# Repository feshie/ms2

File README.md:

# ms2
second version of the feshie node with the z1 replaced with a plug-in arm processor (TI CC2538)

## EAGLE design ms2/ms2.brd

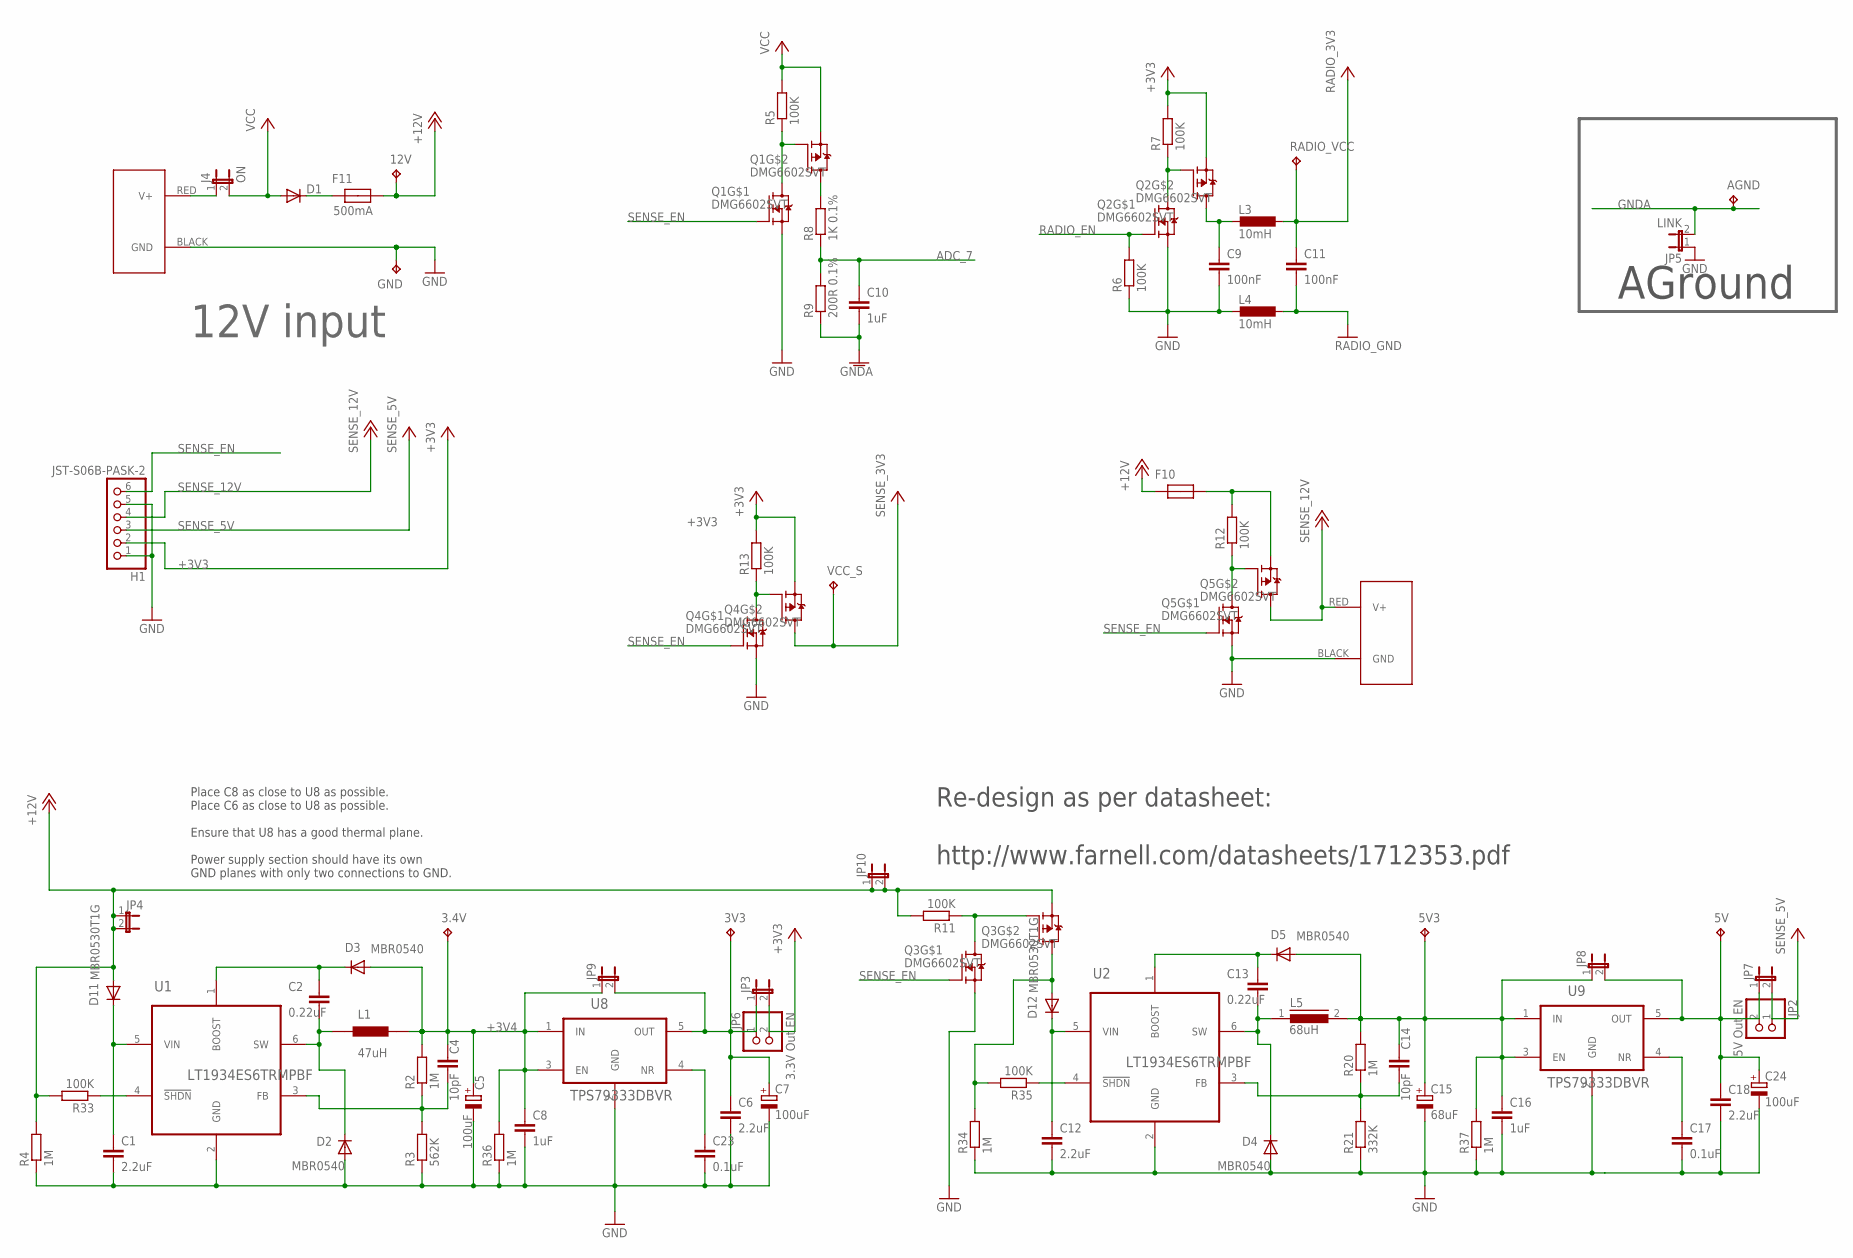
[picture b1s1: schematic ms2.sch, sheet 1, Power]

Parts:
3.4V, 3V3, 12V: TPB2,54; B2,54
5V, 5V3: 5V B; B2,54
12V_OUT: POWERPOLE_POWER45A; POWERPOLE_PAIR_45A
AGND: TPB2,54; B2,54
C1, C6, C12, C18: 2.2uF; C0805
C2, C13: 0.22uF; C0805
C4, C14: 10pF; C0805
C5, C7, C24: 100uF; PANASONIC_E
C8, C10, C16: 1uF; C0805
C9, C11: 100nF; C0805
C15: 68uF; PANASONIC_E
C17, C23: 0.1uF; C0805
D1: DIODE-SMB; SMB
D2, D3, D4, D5: MBR0540; SOD123
D11, D12: MBR0530T1G; SOD123
F10, F11: MCF0805; 0805
GND: 5V B; B2,54
H1: JST-S06B-PASK-2; JST-PA-6-SE
J1: POWERPOLE_POWER45A; POWERPOLE_PAIR_45A
J4: ON; 2-MOLEX
JP2: 5V Out EN; 1X02
JP3, JP4, JP7, JP8, JP9, JP10: JUMPER-2SMD-NO; SJ_2S-NO
JP5: LINK; JP1
JP6: 3.3V Out EN; 1X02
L1: 47uH; 1048
L3, L4: 10mH; L3230M
L5: 68uH; DR127
Q1, Q2, Q3, Q4, Q5: DMG6602SVT; TSOT26
R2, R4, R20, R34, R36, R37: 1M; R0805
R3: 562K; R0805
R5, R6, R7, R11, R12, R13, R33, R35: 100K; R0805
R8: 1K 0.1%; R0805
R9: 200R 0.1%; R0805
R21: 332K; R0805
RADIO_VCC: TPB2,54; B2,54
U1, U2: LT1934ES6TRMPBF; SOT95P280X100-6N
U8, U9: TPS79333DBVR; SOT95P280X145-5N
VCC_S: TPB2,54; B2,54

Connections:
5V3: 5V3.TP, C14.1, C15.+, C16.1, D5.A, JP8.1, L5.2, R20.2, R37.2, U9.1 (IN), U9.3 (EN)
+3V3: H1.2, JP3.2, JP6.2, Q2.P$2 (S), Q4.P$2 (S), R7.2, R13.2; also elsewhere on the board
+3V4: 3.4V.TP, C4.1, C5.+, C8.1, D3.A, JP9.1, L1.2, R2.2, R36.2, U8.1 (IN), U8.3 (EN)
+12V: 12V.TP, D11.A, F10.1, F11.2, JP4.1, JP4.2, JP10.1, JP10.2, Q3.P$2 (S), R4.2, R11.2, R33.2
ADC_7: C10.1, R8.1, R9.2; also elsewhere on the board
GND: 12V_OUT.BLACK (GND), C1.2, C5.-, C6.2, C7.-, C8.2, C9.2, C12.2, C15.-, C16.2, C17.2, C18.2, C23.2, C24.-, D2.A, D4.A, GND.TP, H1.1, H1.5, J1.BLACK (GND), JP5.1, L4.2, Q1.P$5 (S), Q2.P$5 (S), Q3.P$5 (S), Q4.P$5 (S), Q5.P$5 (S), R3.1, R4.1, R6.1, R21.1, R34.1, R36.1, R37.1, U1.2 (GND), U2.2 (GND), U8.2 (GND), U9.2 (GND); also elsewhere on the board
GNDA: AGND.TP, C10.2, JP5.2, R9.1; also elsewhere on the board
unnamed: J1.RED (V+), J4.1
unnamed: C13.1, D5.C, U2.1 (BOOST)
unnamed: D1.C, F11.1
unnamed: C23.1, U8.4 (NR)
unnamed: Q2.P$3 (G), Q2.P$6 (D), R7.1
unnamed: Q1.P$3 (G), Q1.P$6 (D), R5.1
unnamed: 5V.TP, C18.1, C24.+, JP2.2, JP7.1, JP8.2, U9.5 (OUT)
unnamed: C9.1, L3.2, Q2.P$4 (D)
unnamed: Q3.P$3 (G), Q3.P$6 (D), R11.1
unnamed: Q4.P$3 (G), Q4.P$6 (D), R13.1
unnamed: C12.1, D12.C, U2.5 (VIN)
unnamed: C13.2, D4.C, L5.1, U2.6 (SW)
unnamed: C4.2, R2.1, R3.2, U1.3 (FB)
unnamed: 3V3.TP, C6.1, C7.+, JP3.1, JP6.1, JP9.2, U8.5 (OUT)
unnamed: C14.2, R20.1, R21.2, U2.3 (FB)
unnamed: Q5.P$3 (G), Q5.P$6 (D), R12.1
unnamed: F10.2, Q5.P$2 (S), R12.2
unnamed: C1.1, D11.C, U1.5 (VIN)
unnamed: R33.1, U1.4 (!SHDN)
unnamed: R35.1, U2.4 (!SHDN)
unnamed: D12.A, Q3.P$4 (D), R34.2, R35.2
unnamed: C17.1, U9.4 (NR)
unnamed: C2.2, D2.C, L1.1, U1.6 (SW)
unnamed: C2.1, D3.C, U1.1 (BOOST)
RADIO_3V3: C11.1, L3.1, RADIO_VCC.TP; also elsewhere on the board
RADIO_EN: Q2.P$1 (G), R6.2; also elsewhere on the board
RADIO_GND: C11.2, L4.1; also elsewhere on the board
SENSE_3V3: Q4.P$4 (D), VCC_S.TP; also elsewhere on the board
SENSE_5V: H1.3, JP2.1, JP7.2; also elsewhere on the board
SENSE_12V: 12V_OUT.RED (V+), H1.4, Q5.P$4 (D); also elsewhere on the board
SENSE_EN: H1.6, Q1.P$1 (G), Q3.P$1 (G), Q4.P$1 (G), Q5.P$1 (G); also elsewhere on the board
VCC: D1.A, J4.2, Q1.P$2 (S), R5.2; also elsewhere on the board
VCC_HP2_SW1: Q1.P$4 (D), R8.2

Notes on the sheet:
12V input
AGround
Re-design as per datasheet: http://www.farnell.com/datasheets/1712353.pdf
Place C8 as close to U8 as possible. Place C6 as close to U8 as possible. Ensure that U8 has a good thermal plane. Power supply section should have its own GND planes with only two connections to GND.
500mA

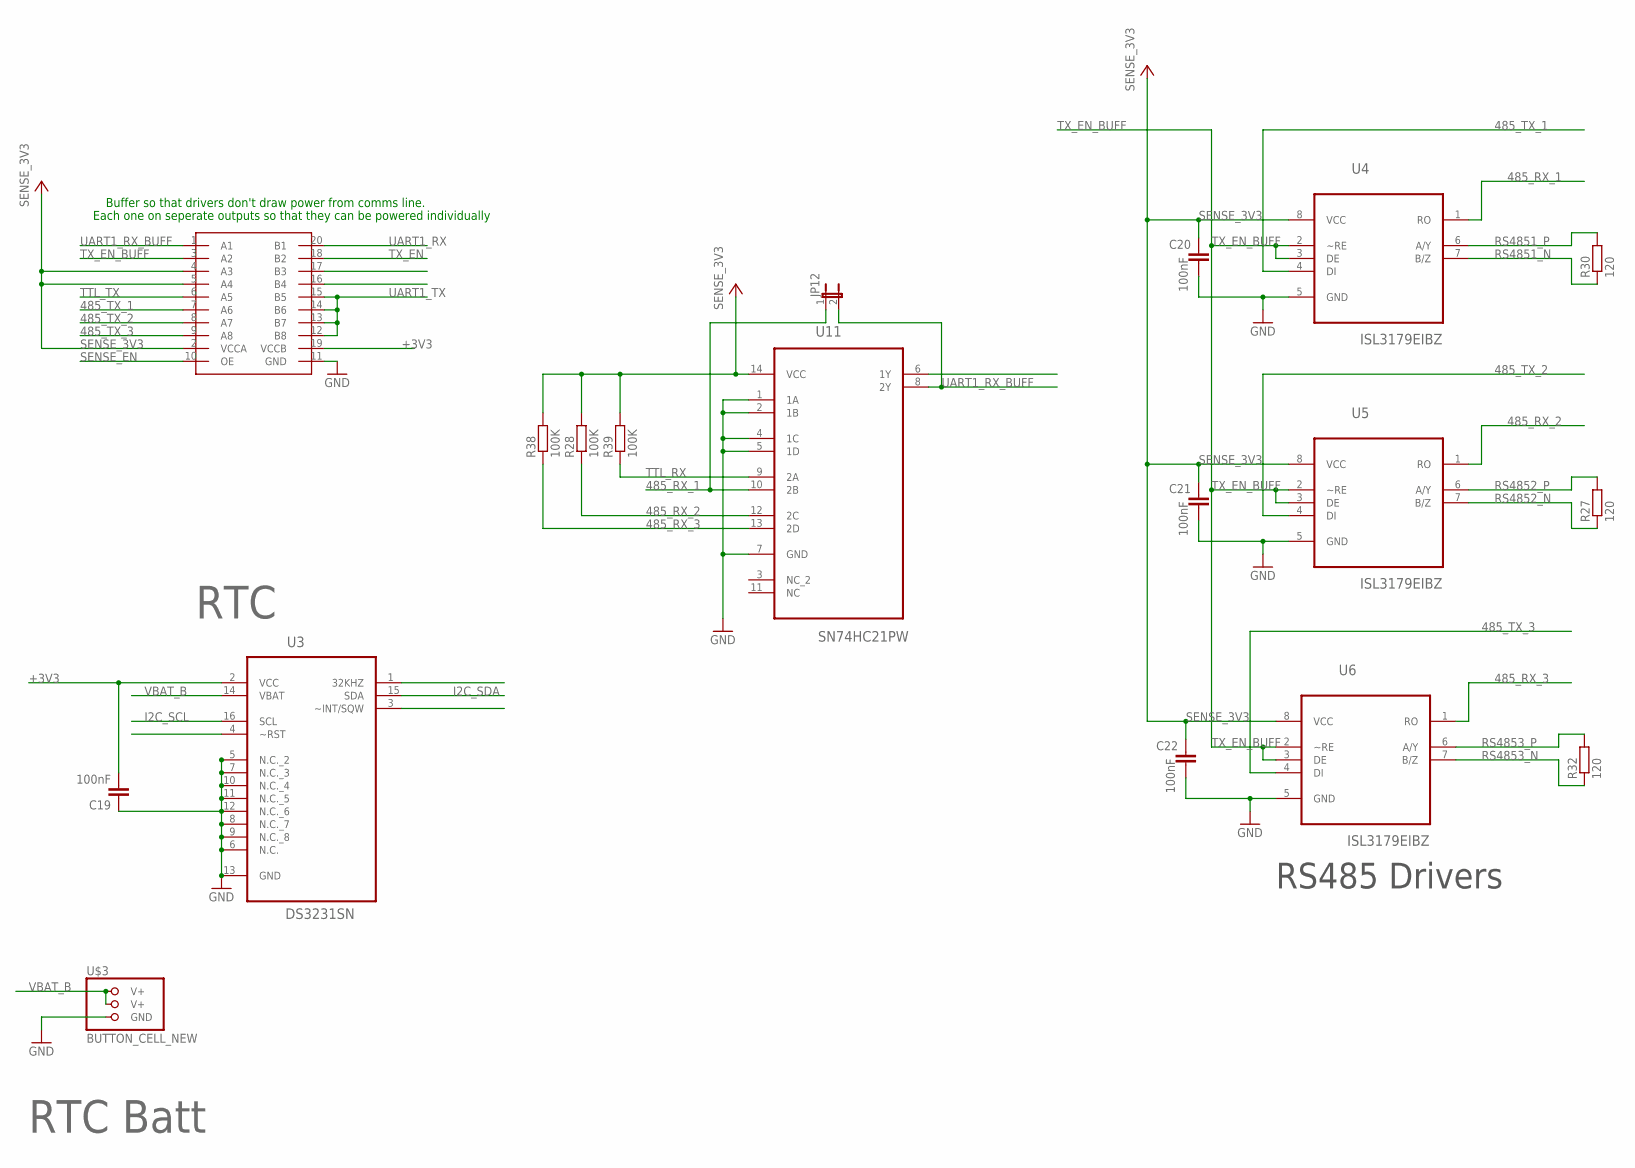
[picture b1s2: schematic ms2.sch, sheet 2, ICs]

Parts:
C19, C20, C21, C22: 100nF; C0805
JP12: JUMPER-2SMD-NO; SJ_2S-NO
R27, R30, R32: 120; R0805
R28, R38, R39: 100K; R0805
U3: DS3231SN; SOIC127P1032X265-16N
U4, U5, U6: ISL3179EIBZ; SOIC127P600X175-8N
U10: TXS0108E; TSSOP20
U11: SN74HC21PW; SOP65P640X120-14N
U$3: BUTTON_CELL_NEW; CR2016

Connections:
485_RX_1: JP12.1, U4.1 (RO), U11.10 (2B)
485_RX_2: R28.1, U5.1 (RO), U11.12 (2C)
485_RX_3: R38.1, U6.1 (RO), U11.13 (2D)
485_TX_1: U4.4 (DI), U10.7 (A6)
485_TX_2: U5.4 (DI), U10.8 (A7)
485_TX_3: U6.4 (DI), U10.9 (A8)
+3V3: C19.2, U3.2 (VCC), U10.19 (VCCB); also elsewhere on the board
GND: C19.1, C20.2, C21.2, C22.2, U3.5 (N.C._2), U3.6 (N.C.), U3.7 (N.C._3), U3.8 (N.C._7), U3.9 (N.C._8), U3.10 (N.C._4), U3.11 (N.C._5), U3.12 (N.C._6), U3.13 (GND), U4.5 (GND), U5.5 (GND), U6.5 (GND), U10.11 (GND), U11.1 (1A), U11.2 (1B), U11.4 (1C), U11.5 (1D), U11.7 (GND), U$3.GND; also elsewhere on the board
I2C_SCL: U3.16 (SCL); also elsewhere on the board
I2C_SDA: U3.15 (SDA); also elsewhere on the board
RS4851_N: R30.1, U4.7 (B/Z); also elsewhere on the board
RS4851_P: R30.2, U4.6 (A/Y); also elsewhere on the board
RS4852_N: R27.1, U5.7 (B/Z); also elsewhere on the board
RS4852_P: R27.2, U5.6 (A/Y); also elsewhere on the board
RS4853_N: R32.1, U6.7 (B/Z); also elsewhere on the board
RS4853_P: R32.2, U6.6 (A/Y); also elsewhere on the board
SENSE_3V3: C20.1, C21.1, C22.1, R28.2, R38.2, R39.2, U4.8 (VCC), U5.8 (VCC), U6.8 (VCC), U10.2 (VCCA), U10.4 (A3), U10.5 (A4), U11.14 (VCC); also elsewhere on the board
SENSE_EN: U10.10 (OE); also elsewhere on the board
TTL_RX: R39.1, U11.9 (2A); also elsewhere on the board
TTL_TX: U10.6 (A5); also elsewhere on the board
TX_EN: U10.18 (B2); also elsewhere on the board
TX_EN_BUFF: U4.2 (~RE), U4.3 (DE), U5.2 (~RE), U5.3 (DE), U6.2 (~RE), U6.3 (DE), U10.3 (A2)
UART1_RX: U10.20 (B1); also elsewhere on the board
UART1_RX_BUFF: JP12.2, U10.1 (A1), U11.8 (2Y)
UART1_TX: U10.12 (B8), U10.13 (B7), U10.14 (B6), U10.15 (B5); also elsewhere on the board
VBAT_B: U3.14 (VBAT), U$3.V+@1 (V+), U$3.V+@2 (V+)

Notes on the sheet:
RTC
RS485 Drivers
Buffer so that drivers don't draw power from comms line.
Each one on seperate outputs so that they can be powered individually
RTC Batt

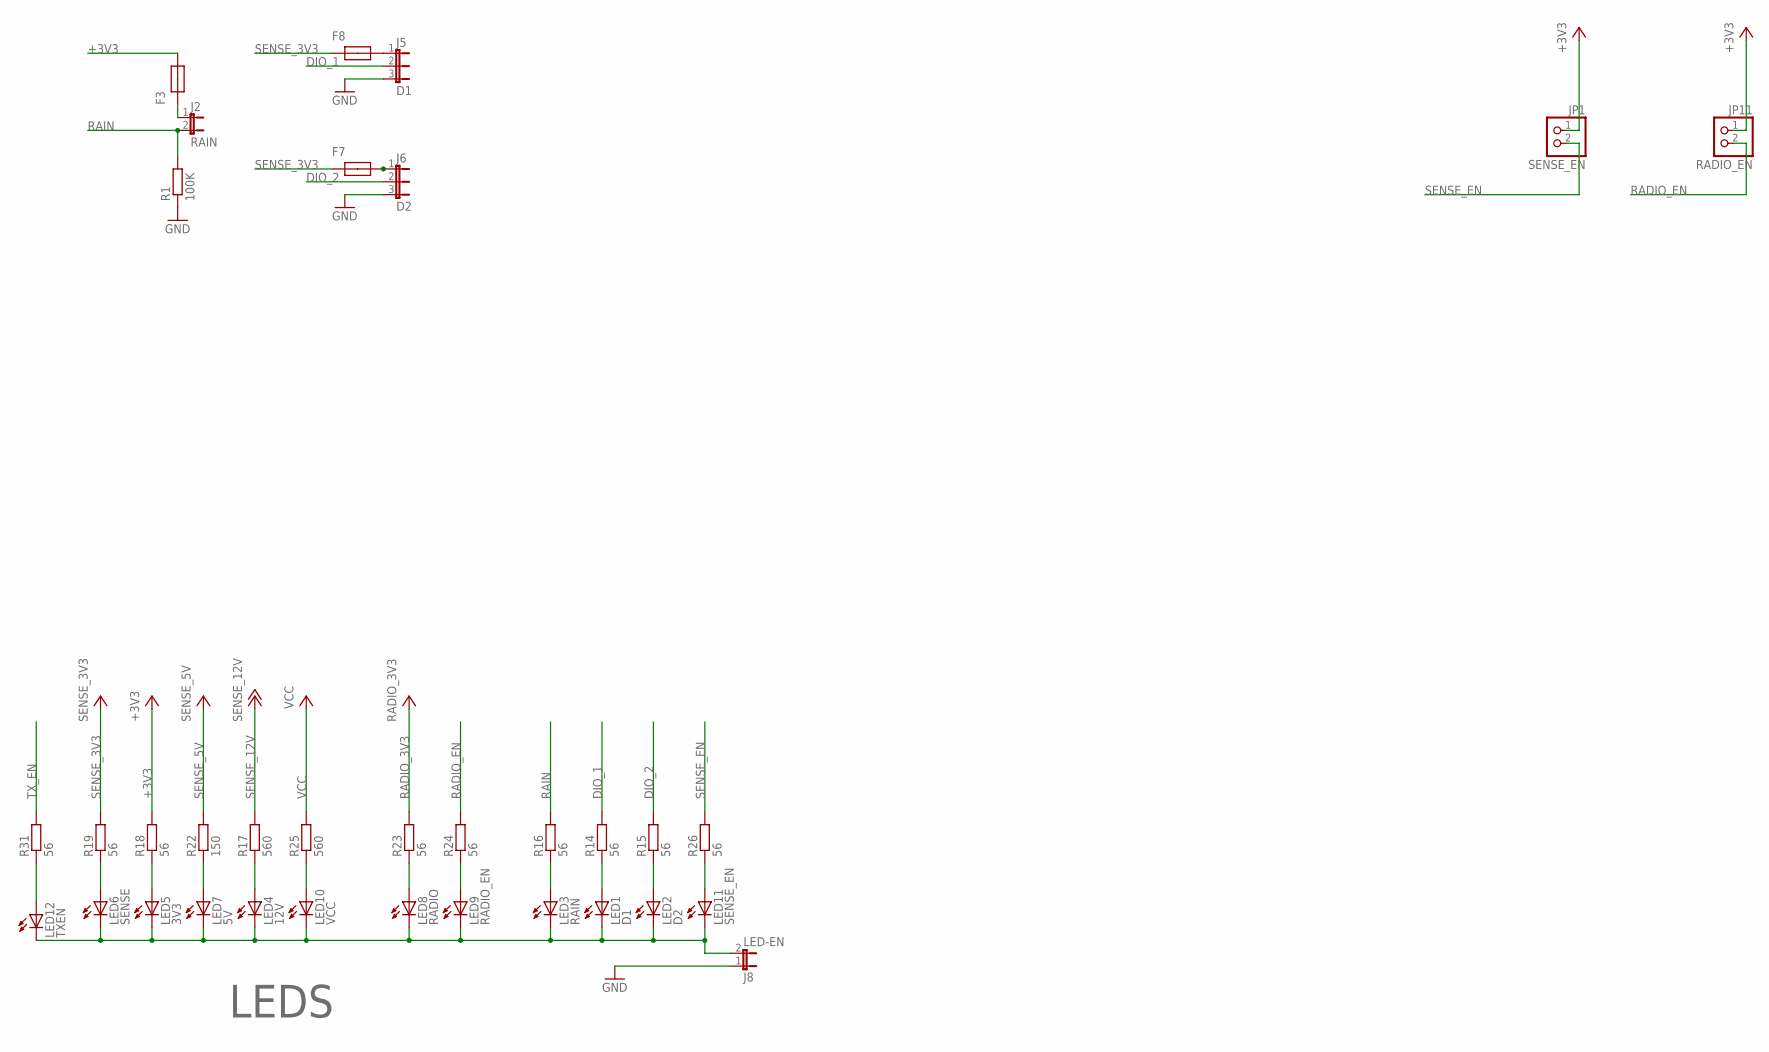
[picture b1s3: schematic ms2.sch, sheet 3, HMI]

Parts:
F3, F7, F8: MCF0805; 0805
J2: RAIN; 2-MOLEX
J5: D1; 3-MOLEX
J6: D2; 3-MOLEX
J8: LED-EN; 2-MOLEX
JP1: SENSE_EN; 1X02
JP11: RADIO_EN; 1X02
LED1: D1; CHIP-LED0805
LED2: D2; CHIP-LED0805
LED3: RAIN; CHIP-LED0805
LED4: 12V; CHIP-LED0805
LED5: 3V3; CHIP-LED0805
LED6: SENSE; CHIP-LED0805
LED7: 5V; CHIP-LED0805
LED8: RADIO; CHIP-LED0805
LED9: RADIO_EN; CHIP-LED0805
LED10: VCC; CHIP-LED0805
LED11: SENSE_EN; CHIP-LED0805
LED12: TXEN; CHIP-LED0805
R1: 100K; R0805
R14, R15, R16, R18, R19, R23, R24, R26, R31: 56; R0805
R17, R25: 560; R0805
R22: 150; R0805

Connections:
+3V3: F3.2, JP1.1, JP11.1, R18.2; also elsewhere on the board
DIO_1: J5.2, R14.2; also elsewhere on the board
DIO_2: J6.2, R15.2; also elsewhere on the board
GND: J5.3, J6.3, J8.1, R1.1; also elsewhere on the board
LGND: J8.2, LED1.C, LED2.C, LED3.C, LED4.C, LED5.C, LED6.C, LED7.C, LED8.C, LED9.C, LED10.C, LED11.C, LED12.C
unnamed: LED4.A, R17.1
unnamed: LED9.A, R24.1
unnamed: LED3.A, R16.1
unnamed: LED2.A, R15.1
unnamed: F7.2, J6.1
unnamed: F8.2, J5.1
unnamed: LED1.A, R14.1
unnamed: F3.1, J2.1
unnamed: LED12.A, R31.1
unnamed: LED11.A, R26.1
unnamed: LED10.A, R25.1
unnamed: LED8.A, R23.1
unnamed: LED7.A, R22.1
unnamed: LED6.A, R19.1
unnamed: LED5.A, R18.1
RADIO_3V3: R23.2; also elsewhere on the board
RADIO_EN: JP11.2, R24.2; also elsewhere on the board
RAIN: J2.2, R1.2, R16.2; also elsewhere on the board
SENSE_3V3: F7.1, F8.1, R19.2; also elsewhere on the board
SENSE_5V: R22.2; also elsewhere on the board
SENSE_12V: R17.2; also elsewhere on the board
SENSE_EN: JP1.2, R26.2; also elsewhere on the board
TX_EN: R31.2; also elsewhere on the board
VCC: R25.2; also elsewhere on the board

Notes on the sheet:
LEDS

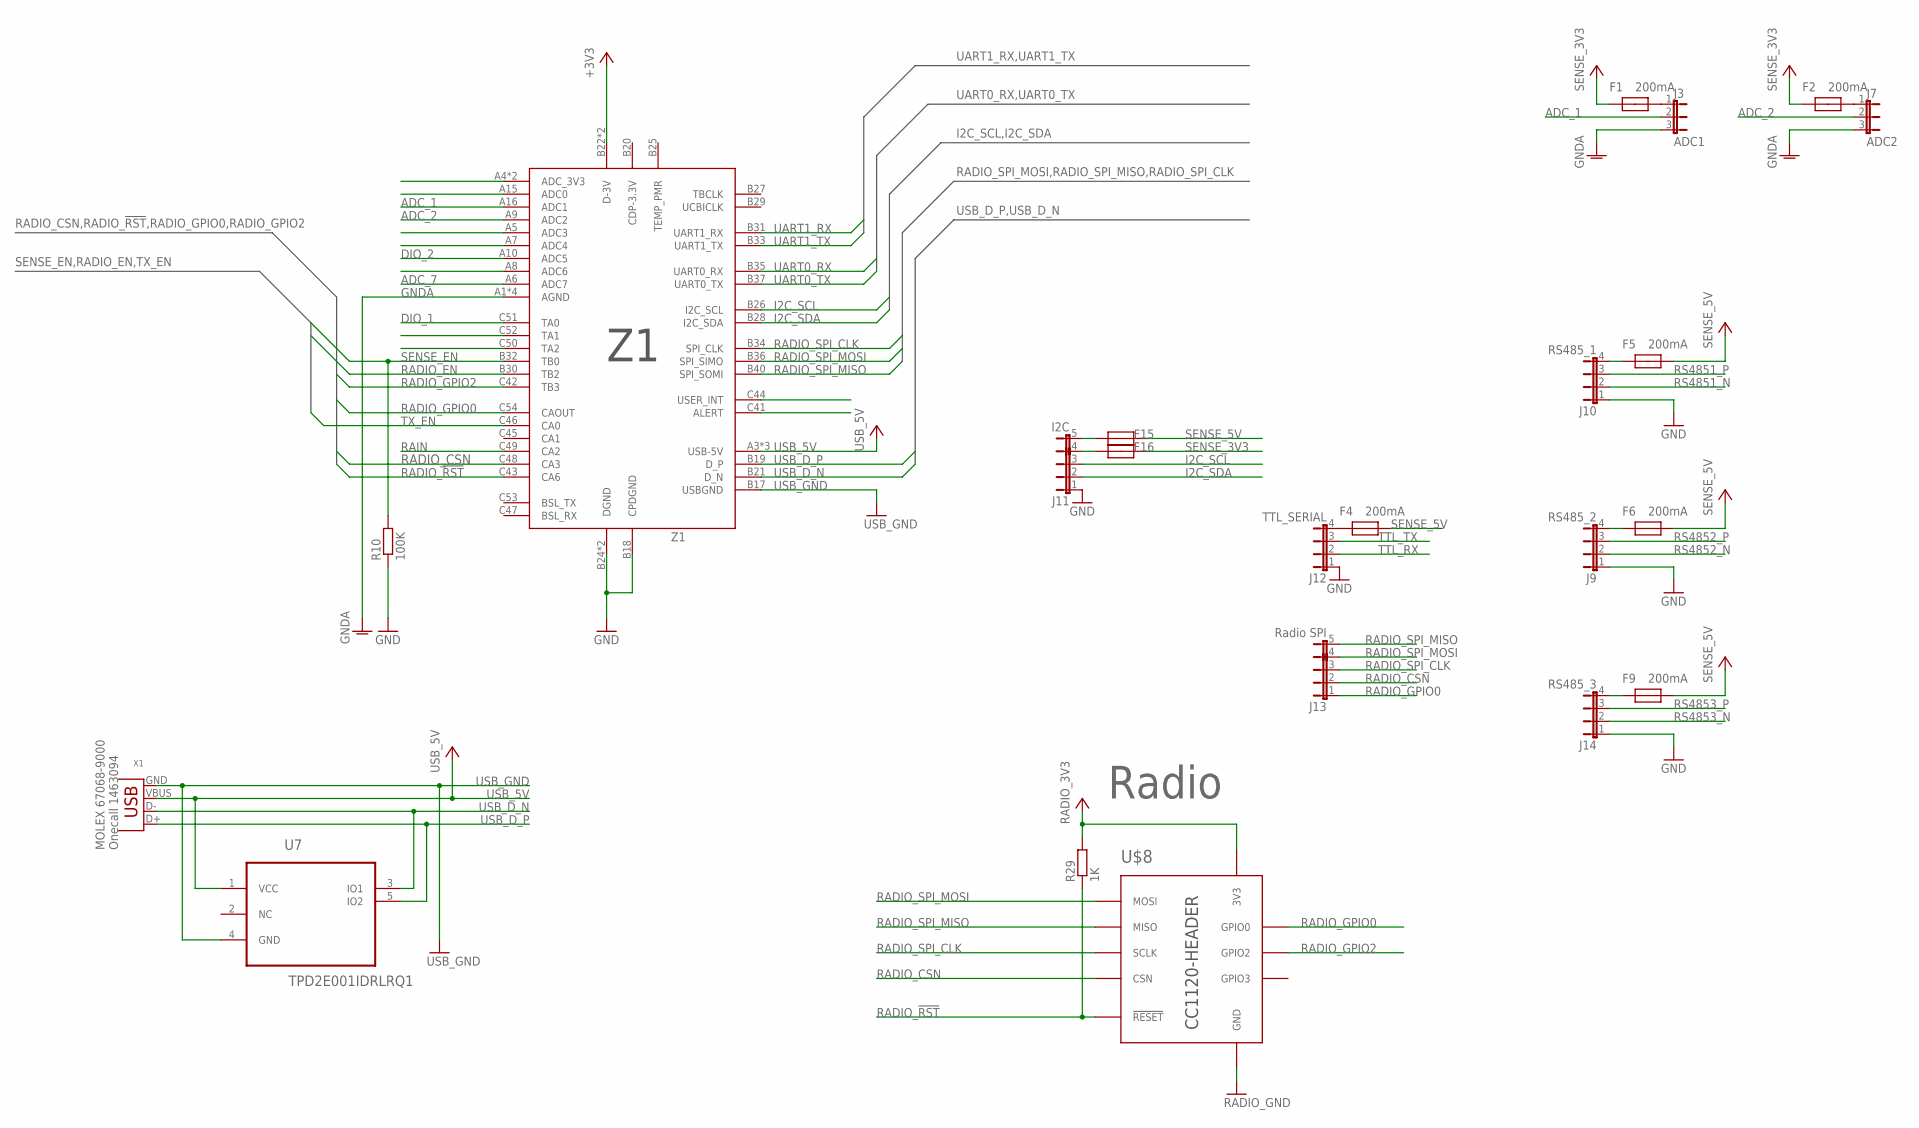
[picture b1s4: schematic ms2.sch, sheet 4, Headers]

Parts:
F1, F2, F4, F5, F6, F9, F15, F16: MCF0805; 0805
J3: ADC1; 3-MOLEX
J7: ADC2; 3-MOLEX
J9: RS485_2; 4-MOLEX
J10: RS485_1; 4-MOLEX
J11: I2C; 5-MOLEX
J12: TTL_SERIAL; 4-MOLEX
J13: Radio SPI; 5-MOLEX
J14: RS485_3; 4-MOLEX
R10: 100K; R0805
R29: 1K; R0805
U7: TPD2E001IDRLRQ1; SOT50P160X60-5N
U$8: CC1120-HEADER-SMT; CC1120-HEADERS-SMT
X1: 67068-9000; USB-B-H
Z1: Z1

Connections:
+3V3: Z1.B22 (D-3V), Z1.C40 (D-3V); also elsewhere on the board
ADC_1: J3.2, Z1.A16 (ADC1)
ADC_2: J7.2, Z1.A9 (ADC2)
ADC_7: Z1.A6 (ADC7); also elsewhere on the board
DIO_1: Z1.C51 (TA0); also elsewhere on the board
DIO_2: Z1.A10 (ADC5); also elsewhere on the board
GND: J9.1, J10.1, J11.1, J12.1, J14.1, R10.1, Z1.B18 (CPDGND), Z1.B24 (DGND), Z1.C39 (DGND); also elsewhere on the board
GNDA: J3.3, J7.3, Z1.A1 (AGND), Z1.A2 (AGND), Z1.A11 (AGND), Z1.A12 (AGND); also elsewhere on the board
I2C_SCL: J11.3, Z1.B26 (I2C_SCL); also elsewhere on the board
I2C_SDA: J11.2, Z1.B28 (I2C_SDA); also elsewhere on the board
unnamed: F5.1, J10.4
unnamed: F6.1, J9.4
unnamed: F4.1, J12.4
unnamed: F9.1, J14.4
unnamed: F1.2, J3.1
unnamed: F2.2, J7.1
unnamed: Z1.A4 (ADC_3V3), Z1.A14 (ADC_3V3)
unnamed: F16.1, J11.4
unnamed: F15.1, J11.5 (6)
RADIO_3V3: R29.2, U$8.3V3-1 (3V3), U$8.3V3-2 (3V3); also elsewhere on the board
RADIO_!RST: R29.1, U$8.RESET (!RESET), Z1.C43 (CA6)
RADIO_CSN: J13.2, U$8.CSN, Z1.C48 (CA3)
RADIO_EN: Z1.B30 (TB2); also elsewhere on the board
RADIO_GND: U$8.GND, U$8.GND1 (GND), U$8.GND2 (GND); also elsewhere on the board
RADIO_GPIO0: J13.1, U$8.GPIO0, Z1.C54 (CAOUT)
RADIO_GPIO2: U$8.GPIO2, Z1.C42 (TB3)
RADIO_SPI_CLK: J13.3, U$8.SCLK, Z1.B34 (SPI_CLK)
RADIO_SPI_MISO: J13.5 (6), U$8.MISO, Z1.B40 (SPI_SOMI)
RADIO_SPI_MOSI: J13.4, U$8.MOSI, Z1.B36 (SPI_SIMO)
RAIN: Z1.C49 (CA2); also elsewhere on the board
RS4851_N: J10.2; also elsewhere on the board
RS4851_P: J10.3; also elsewhere on the board
RS4852_N: J9.2; also elsewhere on the board
RS4852_P: J9.3; also elsewhere on the board
RS4853_N: J14.2; also elsewhere on the board
RS4853_P: J14.3; also elsewhere on the board
SENSE_3V3: F1.1, F2.1, F16.2; also elsewhere on the board
SENSE_5V: F4.2, F5.2, F6.2, F9.2, F15.2; also elsewhere on the board
SENSE_EN: R10.2, Z1.B32 (TB0); also elsewhere on the board
TTL_RX: J12.2; also elsewhere on the board
TTL_TX: J12.3; also elsewhere on the board
TX_EN: Z1.C46 (CA0); also elsewhere on the board
UART0_RX: Z1.B35 (UART0_RX)
UART0_TX: Z1.B37 (UART0_TX)
UART1_RX: Z1.B31 (UART1_RX); also elsewhere on the board
UART1_TX: Z1.B33 (UART1_TX); also elsewhere on the board
USB_5V: U7.1 (VCC), X1.VBUS, Z1.A3 (USB-5V), Z1.A13 (USB-5V), Z1.B23 (USB-5V)
USB_D_N: U7.3 (IO1), X1.D-, Z1.B21 (D_N)
USB_D_P: U7.5 (IO2), X1.D+, Z1.B19 (D_P)
USB_GND: U7.4 (GND), X1.GND, Z1.B17 (USBGND)

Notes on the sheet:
Radio
200mA
MOLEX 67068-9000 Onecall 1463094

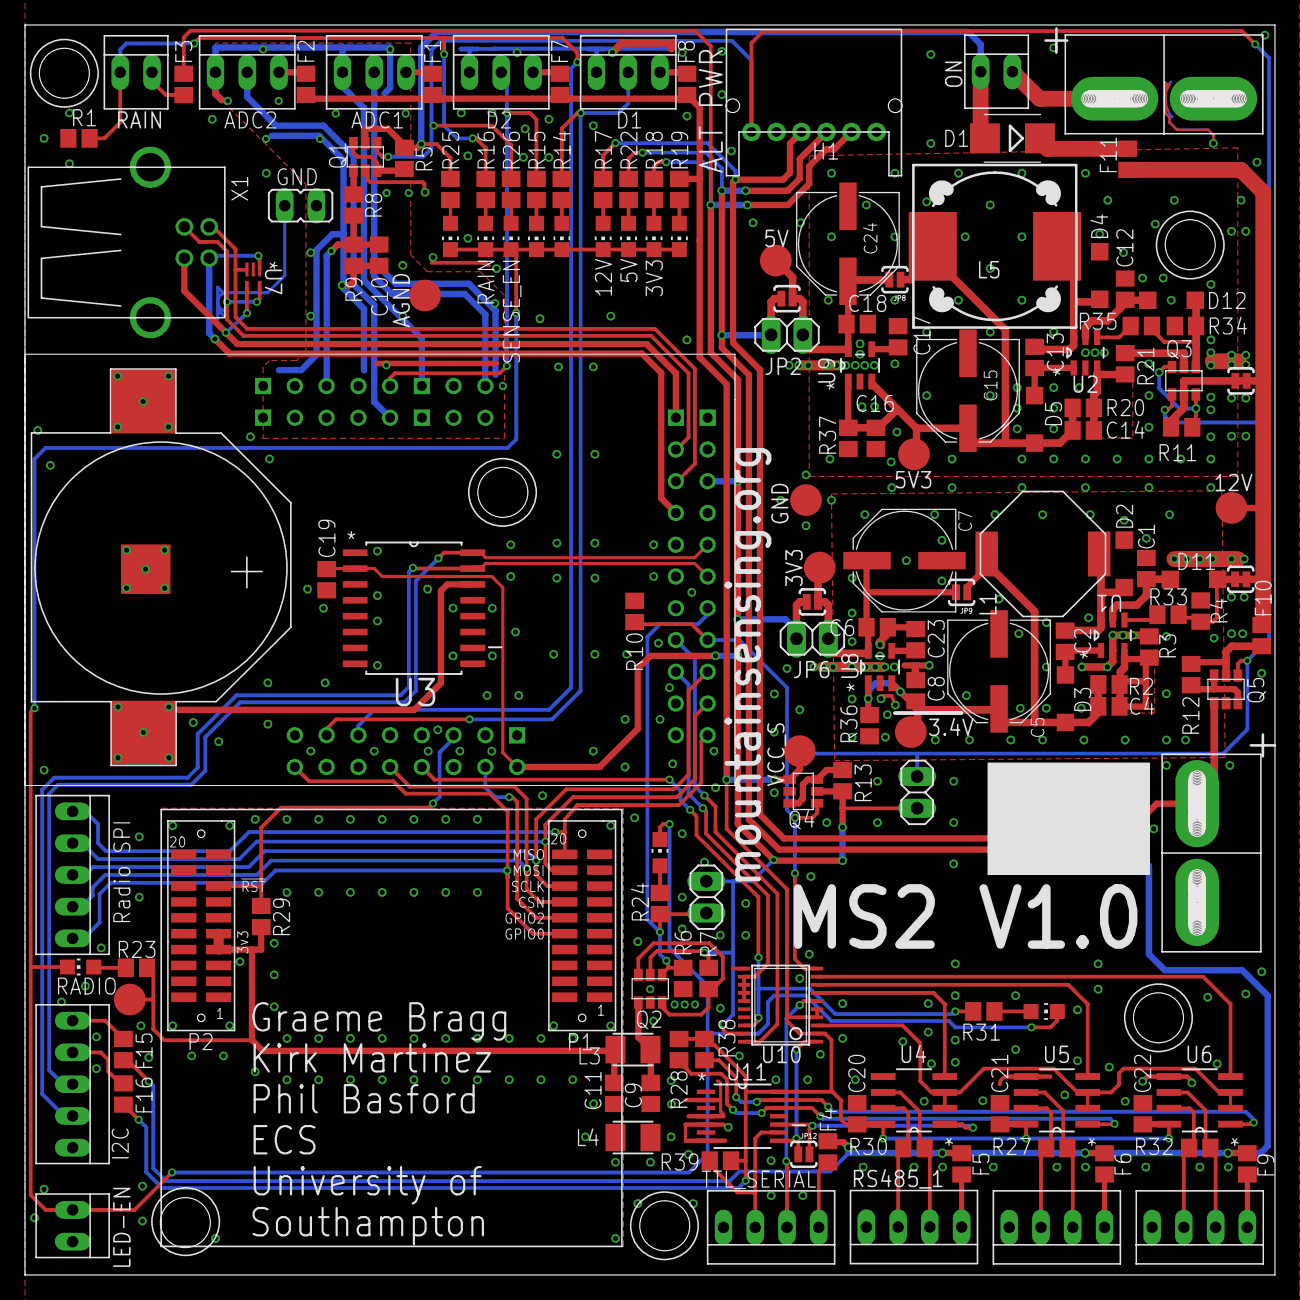
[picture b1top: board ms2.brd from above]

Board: 2 copper layers, 100.0 x 100.0 mm, 155 parts (0 on the bottom side), 103 nets.

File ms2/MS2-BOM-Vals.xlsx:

Qty | Value | Device | Package | Parts | Description | MANUFACTURER | MPN | OC_ONECALL
2 | 10pF | C-EUC0805 | C0805 | C4, C14 | CAPACITOR, European symbol | Multicomp | MC0805N100J500CT | 2320834
2 | 100nF | C-EUC0805 | C0805 | C9, C11, C17, C19, C20, C21, C22, C23 | CAPACITOR, European symbol | Multicomp | MC0805B104K500CT | 1759265
2 | 0.22uF | C-EUC0805 | C0805 | C2, C13 | CAPACITOR, European symbol | Multicomp | MC0805F224Z500CT | 1759269
3 | 1uF | C-EUC0805 | C0805 | C8, C10, C16 | CAPACITOR, European symbol | Multicomp | MC0805X105K250CT | 2320832
1 | 10 | R-EU_R0805 | R0805 | R16 | RESISTOR, European symbol | Multicomp | MCWR08X10R0FTL | 2447556
8 | 68 | R-EU_R0805 | R0805 | R14, R15, R18, R19, R23, R24, R26, R31 | RESISTOR, European symbol | Multicomp | MCHP05W4F680JT5E | 1576443
14 | 100K | R-EU_R0805 | R0805 | R1, R5, R6, R7, R10, R11, R12, R13, R28, R29, R33, R35, R38, R39 | RESISTOR, European symbol | Multicomp | MCHP05W4F1003T5E | 1576493
6 | 1M | R-EU_R0805 | R0805 | R2, R4, R20, R34, R36, R37 | RESISTOR, European symbol | Multicomp | MCHP05W4F1004T5E | 1576507
4 | 2.2uF | C-EUC0805 | C0805 | C1, C6, C12, C18 | CAPACITOR, European symbol | Murata | GRM21BR61H225KA73L | 1845751RL
1 | 68uF | CPOL-EUE | PANASONIC_E | C15 | POLARIZED CAPACITOR, European symbol | Panasonic | EEEFC1E680P | 9693530
3 | 100uF | CPOL-EUE | PANASONIC_E | C5, C7, C24 | POLARIZED CAPACITOR, European symbol | Panasonic | EEEFK1E101P | 9695770
4 | 120 | R-EU_R0805 | R0805 | R22, R27, R30, R32 | RESISTOR, European symbol | Multicomp | MCHP05W4F1200T5E | 1576447RL
2 | 680 | R-EU_R0805 | R0805 | R17, R25 | RESISTOR, European symbol | Multicomp | MCHP05W4F6800T5E | 1576456
1 | 1K 0.1% | R-EU_R0805 | R0805 | R8 | RESISTOR, European symbol | Panasonic | ERA6AEB102V | 1577659
1 | 200R 0.1% | R-EU_R0805 | R0805 | R9 | RESISTOR, European symbol | Panasonic | ERA6AEB201V | 1670217
1 | 332K | R-EU_R0805 | R0805 | R21 | RESISTOR, European symbol | Welwyn | PCF0805R-332KBT1 | 1160284
1 | 562K | R-EU_R0805 | R0805 | R3 | RESISTOR, European symbol | Welwyn | PCF0805R-562KBT1 | 1160297
2 | BEAD | BEAD | 0805 | L3, L4 | INDUCTOR, European symbol | Murata | BLM21PG121SN1D | 2443252RL
1 | 47uH | SRU1048 | 1048 | L1 | CHOKE, POWER, SHIELDED, 47UH, 10mm x 10mm x 4.8mm | Bourns | SRU1048-470Y | 1362022
1 | 68uH | DR127 | DR127 | L5 | INDUCTOR, 68UH, POWER, SHIELDED, SMD | Bourns | SRR1260-680M | 2212503
1 | B130LB-13-F | DIODE-SMB | SMB | D1 | DIODE, REC, SCHOTTKY, 30V, 1A, SMB | Diodes Inc | B130LB-13-F | 1858651
5 | DMG6602SVT | DMG6602SVT | TSOT26 | Q1, Q2, Q3, Q4, Q5 | MOSFET, NP CH, , 30V, 3.4, ATSOT23 | Diodes Inc | DMG6602SVT | 2061522
1 | DS3231SN | DS3231SN | SOIC-16 | U3 | Extremely Accurate I2C-Integrated RTC/TCXO/Crystal | Maxim | DS3231SN | 1593292
3 | ISL3179EIBZ | ISL3179EIBZ | SOIC-8 | U4, U5, U6 | TRANCEIVER | Intersil | ISL3179EIBZ | 1439860
2 | LT1934ES6TRMPBF | LT1934ES6TRMPBF | TSOT-23-6 | U1, U2 | Micropower Step-Down Switching Regulators | Linear Technology | LT1934ES6#TRMPBF | 1663810
2 | MBR0530T1G | MBR0530T1G | SOD123 | D11, D12 | SCHOTTKY BARRIER RECTIFIER | ON Semiconductor | MBR0530T1G | 1431036
4 | MBR0540 | MBR0540T3G | SOD123 | D2, D3, D4, D5 | SCHOTTKY BARRIER RECTIFIER | ON Semiconductor | MBR0540T3G | 2101839
13 | MCF0805 | MCF0805 | 0805 | F1, F2, F3, F4, F5, F6, F7, F8, F9, F10, F11, F15, F16 |  | Bourns | MF-PSMF020X-2 | 1294874RL
6 | LED Green | LEDCHIP-LED0805 | CHIP-LED0805 | LED5, LED8, LED9, LED10, LED11, LED12 | LED | KINGBRIGHT | KPT-2012SGC | 2099239
1 | LED Red | LEDCHIP-LED0805 | CHIP-LED0805 | LED4 | LED | KINGBRIGHT | KPT-2012SURCK | 2099241
1 | LED Orange | LEDCHIP-LED0805 | CHIP-LED0805 | LED2 | LED | KINGBRIGHT | KPT-2012SECK | 2099237
2 | LED Yellow | LEDCHIP-LED0805 | CHIP-LED0805 | LED1, LED6 | LED | KINGBRIGHT | KPT-2012YC | 2099243
2 | LED Blue | LEDCHIP-LED0805 | CHIP-LED0805 | LED3, LED7 | LED | KINGBRIGHT | KPT-2012QBC-D | 2217980
1 | SN74HC21PW | SN74HC21PW | SOP65P640X120-14N | U11 | Triple 3 Input positive NAND gate | Texas Instruments | SN74HC21PW | 1741215
1 | TPD2E001IDRLRQ1 | TPD2E001IDRLRQ1 | SOT50P160X60-5N | U7 | LOW-CAPACITANCE 2-CHANNEL ±15-kV ESD-PROTECTION ARRAY | Texas Instruments | TPD2E001IDRLRQ1 | 2496524
1 | TPS79333DBVR | TPS79333DBVR | SOT-23 | U8 | LOW-DROPOUT LINEAR REGULATORS | Texas Instruments | TPS79333DBVR | 1470478
1 | REG113NA | REG113NA | SOT-23 | U9 | LOW-DROPOUT LINEAR REGULATORS | Texas Instruments | REG113NA | 2342575
1 | TXS0108E | TXS0108E | TSSOP20 | U10 | Texas Instruments TXS0108E | Texas Instruments | TXS0108E | 1702548
1 | BUTTON_CELL_NEW | BUTTON_CELL_NEW | CR2016 | U$3 | CR2032 cell holder | Keystone | 3002 | 1650693
2 | CC1120-HEADER-SMT | CC1120-HEADER-SMT | CC1120-HEADERS-SMT | U$8 | 2x Harwin M50 | HARWIN | M50-3601042 | CN14037

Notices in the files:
parts and their libraries:
SparkFun-Passives: Licensing: Creative Commons ShareAlike 4.0 International - https://creativecommons.org/licenses/by-sa/4.0
